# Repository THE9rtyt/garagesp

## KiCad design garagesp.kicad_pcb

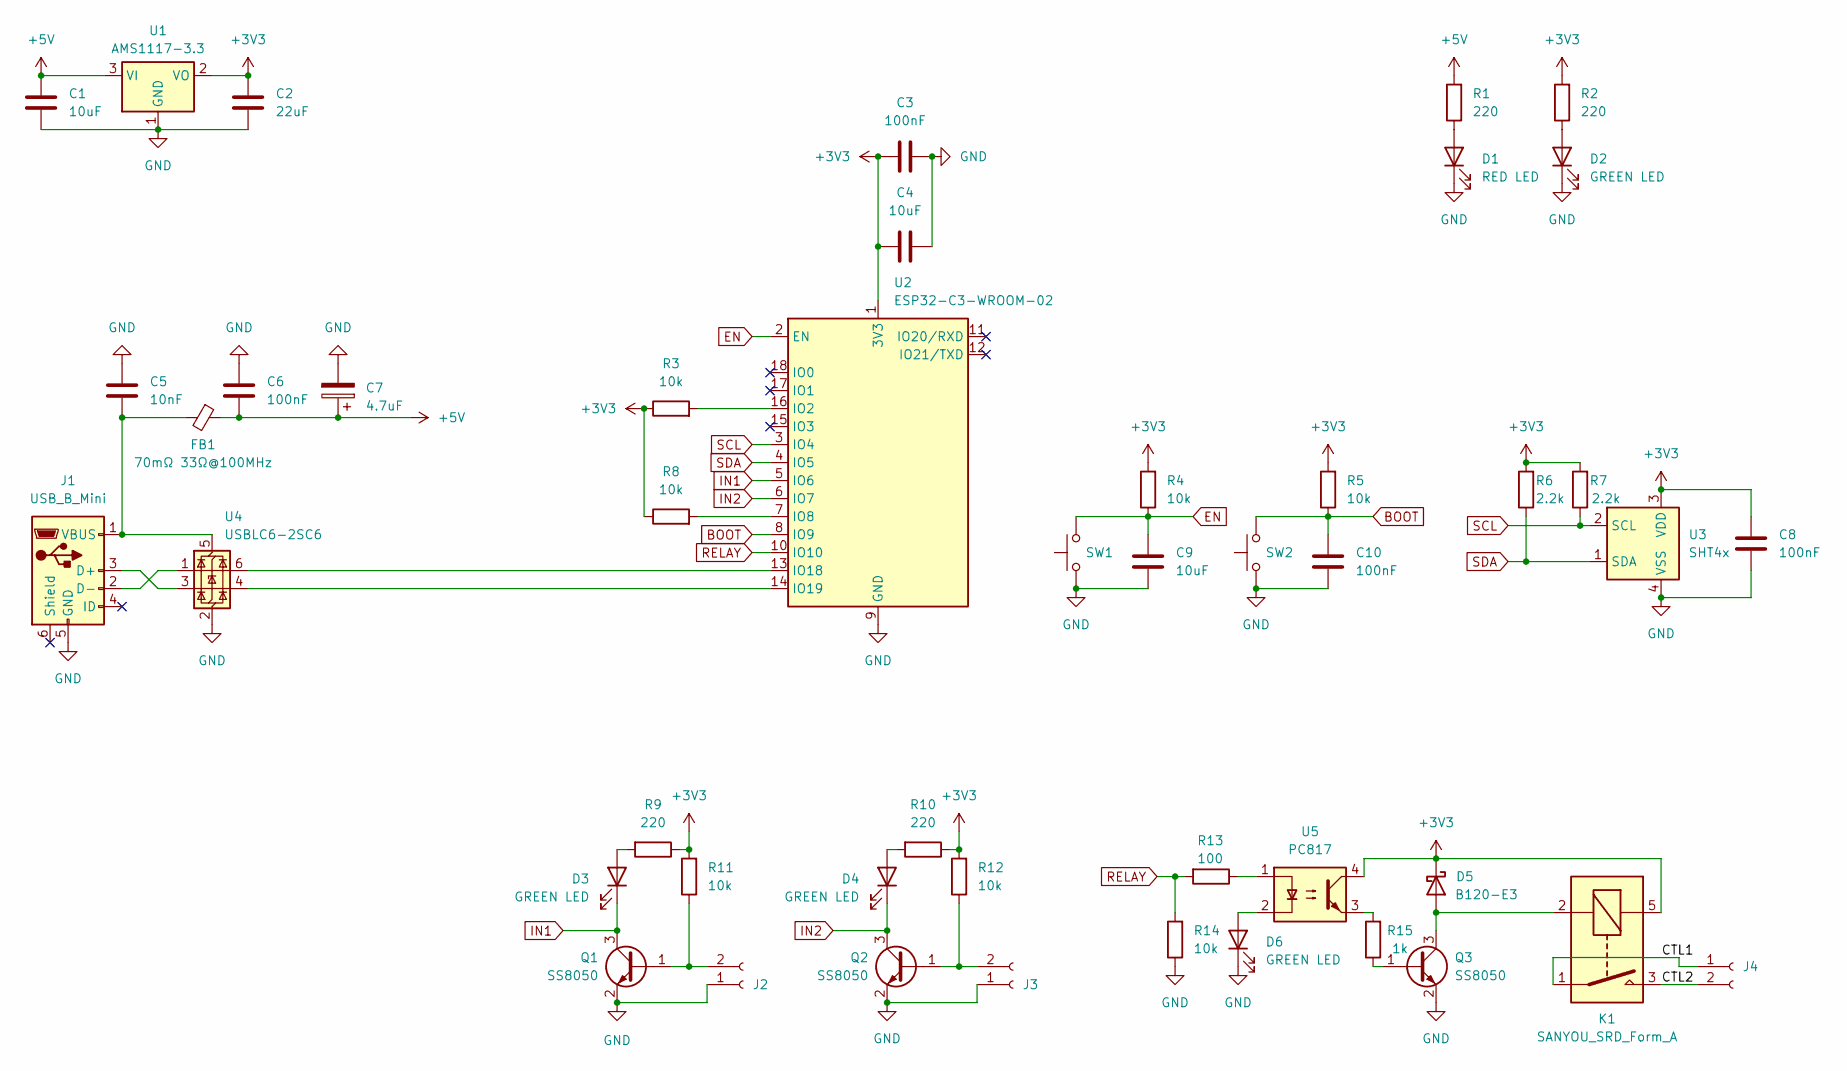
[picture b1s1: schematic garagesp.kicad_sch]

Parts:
C1, C4, C9: 10uF; C_0603_1608Metric_Pad1.08x0.95mm_HandSolder; LCSC C19702
C2: 22uF; C_0603_1608Metric_Pad1.08x0.95mm_HandSolder; LCSC C59461
C3, C6, C10: 100nF; C_0603_1608Metric_Pad1.08x0.95mm_HandSolder; LCSC C14663
C5: 10nF; C_0603_1608Metric_Pad1.08x0.95mm_HandSolder; LCSC C57112
C7: 4.7uF; CP_Elec_4x5.4; LCSC C970652
C8: 100nF; C_0402_1005Metric_Pad0.74x0.62mm_HandSolder; LCSC C1525
D1: RED LED; LED_0603_1608Metric_Pad1.05x0.95mm_HandSolder; LCSC C2286
D2, D3, D4, D6: GREEN LED; LED_0603_1608Metric_Pad1.05x0.95mm_HandSolder; LCSC C2290
D5: B120-E3; D_SMA; LCSC C2902910
FB1: 70mΩ 33Ω@100MHz; L_0805_2012Metric_Pad1.05x1.20mm_HandSolder; LCSC C74764
J1: USB_B_Mini; USB_Mini-B_Lumberg_2486_01_Horizontal; LCSC C136451
J2, J3, J4: Molex_Micro-Fit_3.0_43650-0200_1x02_P3.00mm_Horizontal; LCSC C122431
K1: SANYOU_SRD_Form_A; Relay_SPST_SANYOU_SRD_Series_Form_A; LCSC C140615
Q1, Q2, Q3: SS8050; SOT-23; LCSC C2146
R1, R2, R9, R10: 220; R_0603_1608Metric_Pad0.98x0.95mm_HandSolder; LCSC C22962
R3, R4, R5, R8, R11, R12, R14: 10k; R_0603_1608Metric_Pad0.98x0.95mm_HandSolder; LCSC C25804
R6, R7: 2.2k; R_0603_1608Metric_Pad0.98x0.95mm_HandSolder; LCSC C4190
R13: 100; R_0603_1608Metric_Pad0.98x0.95mm_HandSolder; LCSC C22775
R15: 1k; R_0603_1608Metric_Pad0.98x0.95mm_HandSolder; LCSC C21190
SW1, SW2: SW_SPST_TS-1088-xR020; LCSC C720477
U1: AMS1117-3.3; SOT-223-3_TabPin2; LCSC LCSC
U2: ESP32-C3-WROOM-02; LCSC C2934560
U3: SHT4x; Sensirion_DFN-4_1.5x1.5mm_P0.8mm_SHT4x_NoCentralPad; LCSC C2848306
U4: USBLC6-2SC6; SOT-23-6; LCSC C2827654
U5: PC817; DIP-4_W7.62mm; LCSC C5350

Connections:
+3V3: C2.1, C3.1, C4.1, C8.2, D5.1 (K), K1.5, R2.2, R3.1, R4.2, R5.2, R6.2, R7.2, R8.1, R9.1, R10.1, R11.2, R12.2, U1.2 (VO), U2.1 (3V3), U3.3 (VDD), U5.4
+5V: C1.1, C6.1, C7.1, FB1.1, R1.2, U1.3 (VI)
/CTL1: J4.1, K1.1
/CTL2: J4.2, K1.3
BOOT: C10.2, R5.1, SW2.2, U2.8 (IO9)
EN: C9.1, R4.1, SW1.2, U2.2 (EN)
GND: C1.2, C2.2, C3.2, C4.2, C5.2, C6.2, C7.2, C8.1, C9.2, C10.1, D1.1 (K), D2.1 (K), D6.1 (K), J1.5 (GND), J2.1, J3.1, Q1.2 (E), Q2.2 (E), Q3.2 (E), R14.1, SW1.1, SW2.1, U1.1 (GND), U2.9 (GND), U2.19 (GND), U3.4 (VSS), U4.2 (GND)
IN1: D3.1 (K), Q1.3 (C), U2.5 (IO6)
IN2: D4.1 (K), Q2.3 (C), U2.6 (IO7)
unnamed: D1.2 (A), R1.1
unnamed: D2.2 (A), R2.1
unnamed: D3.2 (A), R9.2
unnamed: D4.2 (A), R10.2
unnamed: D5.2 (A), K1.2, Q3.3 (C)
unnamed: D6.2 (A), U5.2
unnamed: J1.3 (D+), U4.3 (I/O2)
unnamed: J1.2 (D-), U4.1 (I/O1)
unnamed: C5.1, FB1.2, J1.1 (VBUS), U4.5 (VBUS)
unnamed: J2.2, Q1.1 (B), R11.1
unnamed: J3.2, Q2.1 (B), R12.1
unnamed: Q3.1 (B), R15.1
unnamed: R13.1, U5.1
unnamed: R15.2, U5.3
unnamed: R3.2, U2.16 (IO2)
unnamed: R8.2, U2.7 (IO8)
unnamed: U2.13 (IO18), U4.6 (I/O1)
unnamed: U2.14 (IO19), U4.4 (I/O2)
RELAY: R13.2, R14.2, U2.10 (IO10)
SCL: R7.1, U2.3 (IO4), U3.2 (SCL)
SDA: R6.1, U2.4 (IO5), U3.1 (SDA)

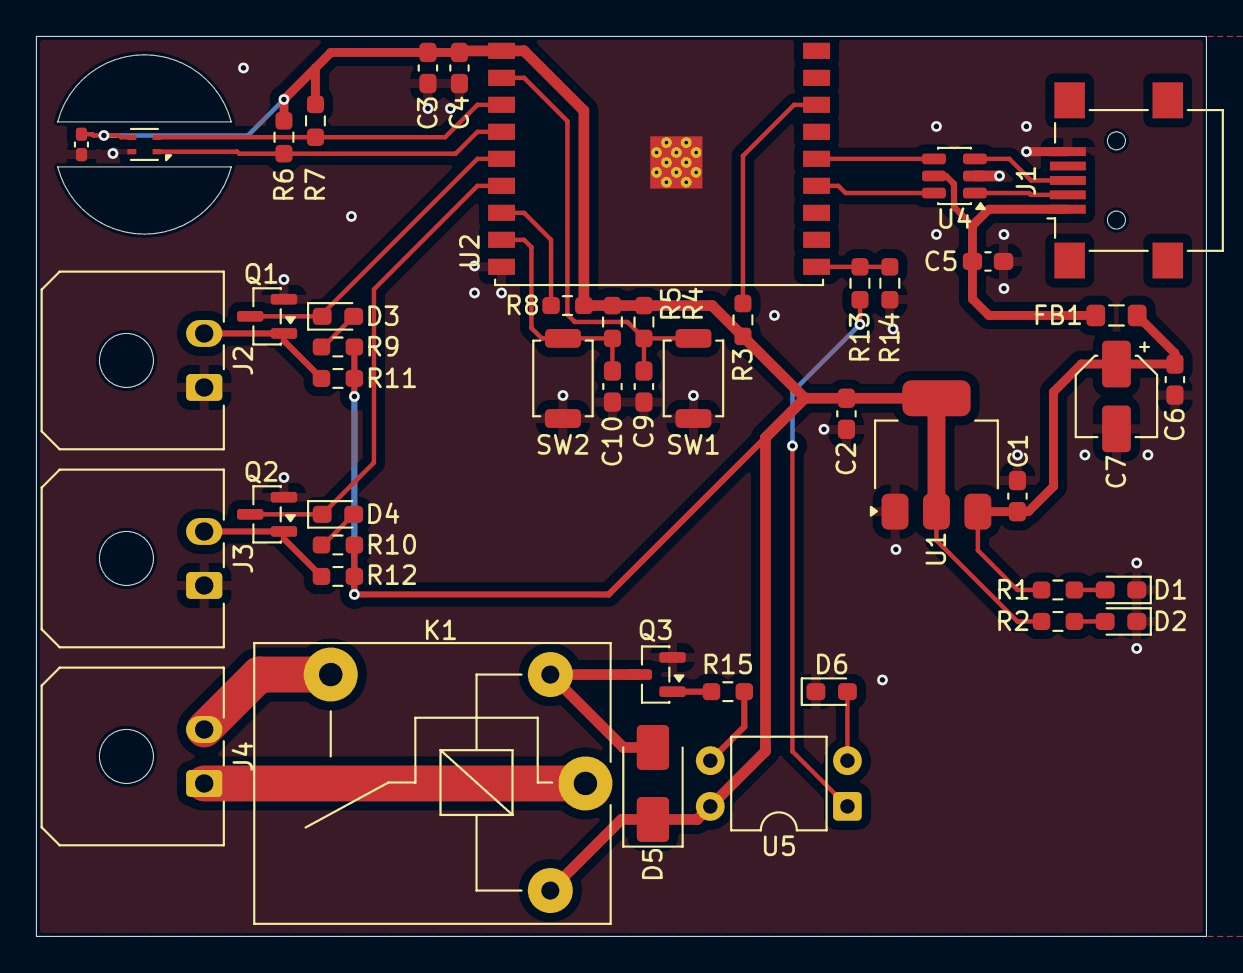
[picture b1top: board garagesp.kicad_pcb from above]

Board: 2 copper layers, 65.0 x 50.0 mm, 47 parts (0 on the bottom side), 30 nets.

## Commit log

2026-02-19 organize things
2026-02-20 move things around again
2026-02-20 finalize placements, add LCSC part #s
2026-02-20 finalize more things
2026-02-20 update schematics
2026-02-23 add capacitors and resistors
2026-02-25 new pcb design
2026-03-08 I like this but want to invert my input LEDs
